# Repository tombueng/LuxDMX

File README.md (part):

<p align="center">
  
</p>

<h1 align="center">LuxDMX</h1>

<p align="center">
  <b>Open-source Art-Net / sACN (E1.31) &rarr; DMX512 gateway for ESP32 / ESP32-S3 / Ethernet.</b>
</p>

<p align="center">
  Its own web page shows all 512 channels live, FPS and jitter per sender, and warns you when
  <b>two consoles fight over a universe</b>. It does RDM too, and a basic one is about 10 EUR in parts.
</p>

<p align="center">

</p>

<p align="center">
  <a href="https://tombueng.github.io/LuxDMX/"><b>Flash from your browser</b></a> &nbsp;·&nbsp;
  <a href="https://luxdmx.org/video"><b>Watch the video</b></a> &nbsp;·&nbsp;
  <a href="#new-the-luxdmx-sequencer"><b>Sequencer</b></a> &nbsp;·&nbsp;
  <a href="hardware-carrier/README.md"><b>DIY carrier board</b></a> &nbsp;·&nbsp;
  <a href="#flashing-pre-built-firmware"><b>Install</b></a>
</p>

## News

**2026-11-12**

- Pixel lights cell by cell: single LEDs in cues, presets, groups and effects
- A console mode with a command line, fixture numbers, faders, encoders and MIDI learn
- Real gobos, prisms and beam angles in the 3D stage
- Endless pan/tilt, a roll axis, moving bars, and winches (they only move while armed)
- Render the 3D stage to a video, up to 8K
- Firmware: the OTA and AP passwords stay out of `/info.json`

Before that: the sequencer came out (11-04), LED rings and matrices (11-07), Apache-2.0 (11-10).
Everything else is in the [version history](CHANGELOG.md).

## New: the LuxDMX Sequencer

<p align="center">
  
</p>

A lighting console in a browser tab. Patch your lights (2,400 fixture types to search), build
looks, add some of the 72 effects and play the show from big buttons, your phone or a song's
timeline. There's a 3D stage, so you can program without any lights. No install, no account, and
your shows stay in your browser. If you know desks: there's a console mode with a command line
("1 thru 4 @ 50", "goto cue 5"), fixed fixture numbers, faders, encoders and MIDI learn, and pixel
lights can be programmed cell by cell (single LEDs of a bar, a ring or a matrix).

It plays a LuxDMX box straight from the page (the box serves a little bridge popup, firmware
v1.0.293 or newer) and any other Art-Net / sACN node through
[LuxDMX Link](sequencer/link/README.md), a small helper for Windows, macOS and Linux.

| | |
|---|---|
|  |  |
|  |  |

<p align="center"><b><a href="https://tombueng.github.io/LuxDMX/sequencer/">Open the Sequencer</a></b> &nbsp;·&nbsp; <a href="sequencer/README.md">What's in it</a> &nbsp;·&nbsp; <a href="sequencer/GUIDE.md">The guide</a></p>

---

| Status page | Settings page |
|---|---|
|  |  |

### The web UI

Manual channel control, labels, sparkline history, identify, blackout and the settings:

**[Watch the video](https://luxdmx.org/video)** &nbsp;·&nbsp; regenerate with [`docs/screenshot.mjs`](docs/screenshot.mjs)

---

## Features

### DMX output

| Feature | Details |
|---|---|
| **Art-Net → DMX512** | Full 512-channel, unicast or broadcast, universe configurable (0–15) |
| **sACN / E1.31 → DMX512** | Multicast receive, universe configurable, runs alongside Art-Net |
| **Protocol selection** | Art-Net only / sACN only / both, set in the web UI |
| **Up to 3 DMX outputs** | Three independent universes, each its own RS485 transceiver (the same universe on several = splitter). All three are RDM-capable |
| **Source merging** | Per-output HTP (highest takes precedence) / LTP (latest wins) / off, honouring the sACN priority field |
| **Signal-loss policy** | Per-output choice when the source stops: hold last frame (default), blackout, or stop sending. Continuous 40 Hz refresh bridges brief input gaps either way |
| **Configurable DMX pins** | Per output: universe, UART port, TX / RX / RTS GPIO, set in the web UI, no recompile |
| **Pixel output (WS281x)** | Drive addressable LED strip from Art-Net or sACN alongside DMX: up to 5 ports, multi-universe per port, WS2812/2815/2811 and SK6812 RGBW, colour order, brightness, gamma, per-port power cap with a live and all-white estimate, and ArtSync / E1.31 sync. Nothing is allocated for a port that is off. See [docs/pixels.md](docs/pixels.md) |

### RDM

| Feature | Details |
|---|---|
| **RDM (E1.20)** | Discover and configure fixtures on the wire: DISC_UNIQUE_BRANCH discovery, GET/SET DEVICE_INFO / DMX start address / identify / sensors, on an RDM-capable output (one with a DE/RE pin). esp_dmx-free RMT-TX + UART-RX engine |
| **RDM over Art-Net** | Full Art-Net 4 RDM output gateway (ArtPoll / ArtTodRequest / ArtTodControl / ArtRdm) so a console (DMX-Workshop, MagicQ, grandMA3, OLA) does RDM to the fixtures over the network. Discovery is scheduled one transaction per DMX frame, so RDM never stalls the DMX output. See [docs/rdm.md](docs/rdm.md) |

### Live diagnostics in the browser

| Feature | Details |
|---|---|
| **Live Web UI** | Bootstrap 5 dark theme, WebSocket push (~10/s), all 512 channels visible |
| **Sender list** | Shows all active Art-Net / sACN senders with per-sender FPS |
| **Conflict detection** | Warning banner when multiple senders are active simultaneously |
| **Jitter stat** | Real-time inter-frame timing deviation (EMA) |
| **Change log** | Live log of DMX value changes with top-N changed channels per frame |
| **Sparkline** | Per-channel history sparkline in the channel detail modal |
| **Channel labels** | Name any channel (e.g. "Front Wash L"), shown in the grid, the channel popup and the change log |

### Manual control

| Feature | Details |
|---|---|
| **Manual DMX control** | Click any channel in browser, set value via slider |
| **Art-Net / Manual toggle** | Switch between protocol passthrough and manual override |
| **Identify** | Flash a channel to full for ~1.5 s to physically locate the fixture |
| **Blackout button** | Zero all channels from the browser |

### Network

| Feature | Details |
|---|---|
| **Ethernet support** | WT32-ETH01 (LAN8720), the carrier board and the v6 board (W5500) run wired LAN *or* WiFi, switchable at runtime; any ESP32 / ESP32-S3 + an external SPI module (W5500 or DM9051) works too, and a **classic ESP32 can pick a SPI chip (W5500 / DM9051) or the built-in MAC + an RMII PHY** (LAN8720, IP101, RTL8201, DP83848, KSZ8081, JL1101) in `/config`; DHCP or static |
| **Selectable network mode** | Pick the interface (WiFi or wired Ethernet) and WiFi mode (client/STA or standalone AP) in the web UI, on boards that have both |
| **Static IP or DHCP** | Configurable static IP/gateway/subnet/DNS, or automatic DHCP |
| **Mesh-aware WiFi** | Scans all channels and joins the **strongest** AP (multi-AP/mesh friendly) |
| **First-run setup portal** | On first boot (or BOOT-button held) LuxDMX opens its own `LuxDMX-setup` access point with a captive portal. From there you either join your WiFi or run the device as its own access point, no router needed |
| **Standalone AP mode** | LuxDMX hosts its own WiFi network so a phone/tablet/console connects directly and sends Art-Net with no router (reachable at `192.168.4.1`) |
| **Wired link-loss policy** | Pick what happens if wired Ethernet is selected but the link is down: keep retrying (default, never opens a hotspot), a standalone WPA2 AP, reboot, or fall back to your saved WiFi network. A runtime watchdog applies it even if the cable is pulled mid-run, and the fallback AP never opens *unsecured*. The WiFi setup portal is BOOT-button-only (physical access), never an automatic fallback |
| **mDNS + DHCP hostname** | Reachable as `dmx-gateway.local` via mDNS, *and* the device sends its hostname over DHCP (option 12) so your router registers it by plain name. Clients without mDNS (e.g. Windows) can then reach it as `dmx-gateway` / `dmx-gateway.fritz.box`. Hostname configurable |

### Remote config from the console

| Feature | Details |
|---|---|
| **Remote node config (ArtAddress)** | Configure the node from the console's own network window (MagicQ Network Manager, DMX-Workshop, ...): rename it and move each output to a different universe, saved to NVS so it survives a reboot. On by default and **unauthenticated**, like every other Art-Net command. See [Remote node config over Art-Net](#remote-node-config-over-art-net-artaddress) |
| **Remote IP config (ArtIpProg)** | A controller can read and set the node's IP / mask / gateway (or switch it to DHCP) over the network with Art-Net `ArtIpProg`, so a box that landed on an unreachable address is recoverable without the BOOT button or a serial cable. **Off by default** (Art-Net has no auth, so on = anyone on the wire can renumber it); the new address applies on the next boot. See [Remote IP config over Art-Net](#remote-ip-config-over-art-net-artipprog-off-by-default) |

### On the box

| Feature | Details |
|---|---|
| **Status LED** | Plain GPIO, WS2812 RGB NeoPixel, or 5-LED panel (v6 board), all showing the same states: green = up (stays on; slow blink = DMX coming in), blue = RDM/identify **added on top of green** (both LEDs on the panel, cyan on a single RGB LED), orange = Ethernet-on-WiFi-fallback, red = no network, Knight-Rider boot |
| **Status display** | Optional I²C OLED (SSD1306 / SH1106) or colour SPI OLED (SSD1351): IP, universe, FPS, sources + auto-rotating conflict/identify/manual banners |
| **On-unit controls** | Optional rotary encoder and/or up to 4 buttons drive a small on-display menu to set the universe (and protocol) without a phone or PC, and the choice persists. Works with any mix of inputs: encoder only, one button, or the lot. See [docs/controls.md](docs/controls.md) |

### Updates, settings and API

| Feature | Details |
|---|---|
| **Versioned OTA** | Pick & install any past release from a table, or auto-update to latest |
| **OTA Updates** | ArduinoOTA (IDE/CLI) + manual `.bin` upload + one-click update from luxdmx.org |
| **NVS persistence** | Universe, protocol, IP config, labels, hostname, OTA password, LED/DMX pin config survive reboots |
| **Config backup / restore** | **`/config` → Backup & Restore**: download every setting plus the channel labels as one `.json`, restore it later or onto another box of the same kind. Passwords stay out unless you tick the box. A file may hold just a few settings; only those change. See [Backup and restore](#backup-and-restore) |
| **Config reset** | Hold BOOT button 3 s on startup, or via `/reset` page |
| **Remote restart** | Restart the box from the web UI (**Device → Restart device**) or `POST /reboot`, without changing a setting. Useful when a long-running gateway needs a nudge, or to free up memory before a firmware update |
| **REST API** | `GET /dmx.json`, `/senders.json`, `/log.json`, `/version.json`, `/labels.json` |
| **Browser bridge** | A web page can send DMX to the box (the [LuxDMX Sequencer](sequencer/README.md) does): the box serves `/bridge`, a tiny page the app opens as a popup, which asks you once per site and forwards frames over `/ws`. Shown as a sender with protocol **Web**, merged like any other source. See [Sending DMX from a web page](#sending-dmx-from-a-web-page-the-bridge) |
| **Phone as a remote** | The box serves `/remote`: a phone scans the sequencer's QR code and plays the laptop's live page (buttons, faders, GO, blackout) through the box. Held buttons let go by themselves if the phone drops out. See [A phone as a remote](#a-phone-as-a-remote) |

### Boards

| Feature | Details |
|---|---|
| **Firmware builds** | ESP32 (WROOM-32), ESP32-S3 (DevKitC-1), ESP32-S3 with octal PSRAM, WT32-ETH01. Plus a catalog of 30-odd boards in the `/config` pin picker, see [Visual pin configuration](#visual-pin-configuration-board-picker) |
| **DIY carrier board** | A 2-layer PCB for off-the-shelf modules: ESP32-S3 N16R8, up to 3 DMX/RDM ports, up to 5 pixel ports, W5500, OLED, encoder and buttons. Hand-solderable, a few bucks in parts. See [Hardware](#hardware) |

---

## Hardware

The easy way to a real LuxDMX box is the carrier board below: order the PCB, plug in modules,
solder a few small parts. If you just want to try it tonight, skip to the
[breadboard build](#breadboard-build-no-pcb), that's an ESP32 and one RS-485 module on jumper wires.

> ### The LuxDMX carrier board
>
> The DIY path, for a few bucks. A 2-layer PCB that off-the-shelf modules plug into: an
> **ESP32-S3-DevKitC-1 N16R8**, up to three **MAX3485** RS-485 modules, a **USR-ES1 W5500** for
> wired Ethernet and a **1.3" SH1106 OLED**. The rotary encoder and two buttons sit right on the
> board. Everything else is a handful of small parts on the back, and those are all optional
> except the ones for what you actually use.
>
> - **DMX + RDM on up to 3 ports**, one RS-485 module per port, direction pin driven so RDM works
> - **WS281x pixels on up to 5 ports** once you add the 74HCT541 buffer chip. It lifts the S3's
>   3.3 V data to the 5 V the strips want, so no pixels without it
> - **WiFi**, or wired Ethernet when the W5500 module is fitted
> - 12/24 V pixel supply with a fuse on the board; the logic runs off USB, an external 5 V or a
>   little buck module off the pixel supply
> - 100 x 80 mm, any fab. Hand soldering only, and the lands take anything from 0402 to 1206, so
>   use whatever's in your drawer
>
> A one-port WiFi DMX node is around 10 EUR of parts off AliExpress, plus the PCB. Ethernet and the
> display add another 6 to 11.
>
> Most of the firmware testing happens on this board. The DMX ports are **not galvanically
> isolated** (plain MAX3485 modules, TVS diodes on the lines). Fine for a desk or a small rig. If
> you need isolation, the breadboard build with the Waveshare module has it.
>
> 
>
> **→ Gerbers, BOM with LCSC numbers, assembly guide and the current math: [`hardware-carrier/`](hardware-carrier/README.md)**

### Carrier: what plugs in

| Module | Search for | Watch out |
|---|---|---|
| ESP32-S3 dev board | `ESP32-S3-DevKitC-1 N16R8` | Get the N16R8 (16 MB flash, 8 MB octal PSRAM), that's what the carrier build expects. The socket rows are **25.4 mm** apart, one pitch wider than Espressif's own DevKitC-1 (22.86 mm), which is what the common dual USB-C clones have. Hold the seller's photo against a 1:1 print of the footprint before you buy |
| RS-485, one per DMX port | `MAX3485 TTL to RS485 module 3.3V` | The bench board runs the RAKSTORE one, silk `RS485 V2.01`. Needs the **EN pin**, without it there is no RDM. Most carry 120 Ω and bias already, see the terminator below |
| Ethernet (optional) | `USR-ES1 W5500` | Two rows of 6 pins. The W5500 boards with 8 pins in one row are a different module |
| Display (optional) | `1.3 inch OLED I2C SH1106` | Sits on a 1x4 female socket. These ship with VCC and GND in either order, check its own silk |

### Carrier: optional parts

Only the ESP32 module is mandatory. A two-port DMX node without pixels leaves more than half the
board empty. The small parts all sit on the back under the modules, so solder those first, then the
headers.

| Part | Fit it when |
|---|---|
| **DMX, per port** | |
| MAX3485 module + 3-pin header (or a 2.54 mm screw terminal) | you use that port |
| 10k on DE/RE | you use that port. Keeps the driver off the bus while the ESP boots |
| 120 Ω terminator | that port is at the **end** of the bus, and the module doesn't already have one (a second one puts 60 Ω on the bus) |
| 2 × 330 Ω fail-safe bias | the port drives its bus, which it normally does. Once per bus, so leave it out if the module already biases the line |
| 2 × TVS diode (SMF12CA or SMAJ12CA) | the port leaves the enclosure |
| **Pixels** | |
| 74HCT541 buffer (SO-20 wide) | at least one pixel port is used. **HCT**, not HC: the HC parts don't switch reliably on 3.3 V. And not the `PW` (TSSOP) version LCSC stocks most of, it won't land |
| 330 Ω series resistor, per port | you use that pixel port. Damps the ringing on the strip wire |
| 3-pole screw terminal, per port | you use that pixel port |
| 1000 µF 35 V, `12-24V IN` terminal, fuse | any pixel port is used, see power below |
| **Network and UI** | |
| W5500 module + 2 × 10k pull-ups + 100 nF / 1 µF / 22 µF | you want wired Ethernet |
| 1.3" OLED | you want the display |
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
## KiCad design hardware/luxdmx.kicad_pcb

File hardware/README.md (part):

> [!NOTE]
> **v6 has not been fabricated yet.** The board is on `master`, design-complete, and passes the full
> scripted validation (DRC, isolation, SPICE, Ethernet skew, header parity; see **VALIDATION.md**).
> An earlier spin of this design was built and came up working (rails, galvanic isolation, PoE
> standalone, both DMX universes bit-exact, RDM 64/64 on both lines), but v6 carries changes that
> have not been on physical copper yet: native USB instead of a CH340 bridge, TPS2116 priority mode,
> a 3225 crystal package, and the J4/J6 header re-pin. Those are what the first v6 article has to
> prove. Treat it as a prototype: the firmware on a plain ESP32 + an isolated RS-485 module is still
> the longest-proven path (see the main README). The ruggedization pass (USB ESD, PTC fuse, +5V TVS,
> a TPS2116 priority power mux, DMX common-mode chokes, ferrite supply filters), plated GND mounting
> holes, wider power traces, and the DMX512-A "Protected" series-TBU front end are all in.

# LuxDMX v6 — hardware

A compact, open-source **Art-Net / sACN → galvanically-isolated DMX512 gateway**, built around
an ESP32-S3 with **both** WiFi *and* wired Ethernet. Designed entirely as code (SKiDL netlist) and
routed by a fully-scripted, placement-driven pipeline — so the board regenerates itself from your
component placement, isolation barrier and all.

---

## What problem does it solve?

Lighting consoles and media servers speak **Art-Net** or **sACN (E1.31)** over a network. Fixtures —
dimmers, moving heads, hazers, LED bars — speak **DMX512** over an isolated RS-485 bus. LuxDMX sits
between them: it receives Art-Net/sACN over WiFi or Ethernet and emits a clean, **opto-isolated DMX512**
signal. It's the box that lets you drive a rack of conventional stage gear from QLab, a grandMA, or any
Art-Net source — without dragging a laptop and a USB-DMX dongle around backstage.

The whole device runs on a single ESP32-S3, fits on a board you can hold in your palm, and costs a few
dollars to fabricate at JLCPCB.

---

## Headline design decisions (the "why")

| Decision | Why |
|---|---|
| **ESP32-S3** as the MCU | Plenty of GPIO, fast dual-core, native USB, mature Arduino/IDF support, and cheap. The **N8R2** brings 8 MB flash + **2 MB PSRAM**, and because that PSRAM is **quad**, it leaves **GPIO35–37** free for the expansion header. Only the **octal**-PSRAM parts (R8 and up) wire GPIO33–37 to the memory and lose them. |
| **W5500 SPI Ethernet** (not the ESP's RMII) | The S3 has **no built-in Ethernet MAC** (unlike the original ESP32), so RMII/LAN8720 is physically impossible. The W5500 is a self-contained TCP/IP-offload Ethernet controller on SPI — the *only* practical wired-Ethernet path for the S3. Wired Ethernet matters: a packed venue's 2.4 GHz band is hostile, and a show can't drop frames. |
| **Galvanically-isolated DMX** | DMX runs long cables between gear sitting on different mains circuits with different ground potentials. Without isolation you get **ground loops** (noise, flicker) and, worse, **fault currents** that can destroy the gateway when something downstream shorts. Pro DMX gear is *always* isolated. We isolate both the data (ISO3086) and the power feeding it (B0505S DC-DC), so the DMX domain shares **no copper** with the logic side. |
| **USB-C** | Reversible, modern, and carries both **power and native flashing** — one cable to power and program. |
| **4-layer PCB** | A solid inner ground plane gives the W5500's Ethernet pairs a 100 Ω reference, tames EMI, and makes the dense routing actually fit. (More below.) |

---

## The components, in detail

### Brains & networking
- **U1 — ESP32-S3-WROOM-1-N8R2** *(LCSC C2913204; 8 MB flash + 2 MB quad PSRAM)* — the MCU + 2.4 GHz WiFi radio. Runs the Art-Net/sACN
  receiver, the web UI, OTA updates, and the DMX engine. The PCB antenna hangs over the left board edge
  (no copper underneath it — intentional, for radiation efficiency).
- **U2 — WIZnet W5500** *(C32843)* + **Y1 — 25 MHz crystal, 3225** *(C9006, CL = 12 pF, load caps C12/C13 = 18 pF C0G)* + **J3 — HY931147C PoE RJ45 MagJack** *(C91754)* —
  a complete 10/100 wired-Ethernet subsystem on SPI. The magjack integrates the isolation magnetics,
  the link/activity LEDs, **and an internal PoE rectifier** (Mode A + Mode B → a single rectified DC pair
  on pins 9/10 — see *Power*). (Ethernet is isolated by the magjack's transformers; the W5500's
  current-mode TX center-tap is biased to 3V3 on the chip-side tap, independent of the PoE extraction
  on the cable side.)

### Isolated DMX output — two independent universes
Each universe is a self-contained galvanic island; the two share no copper with each other or the logic side.
- **U5 / U6 — TI ISO3086DWR** *(C183095)* — the **isolated RS-485 transceivers** (one per universe). The DMX
  driver and the logic that controls it are separated by a silicon isolation barrier rated for kilovolts.
  Wired 2-wire (Y↔A, Z↔B bridged) for standard DMX512. Universe 1 on UART/port 1, universe 2 on port 2.
- **PS1 / PS2 — B0505S-1W** *(C7465127)* — the **isolated 5 V→5 V DC-DC** modules powering the *secondary*
  side of U5 / U6. Because both the data path **and** its power are isolated, each DMX connector shares no
  ground with anything else.
- **D1 / D7 — SM712 TVS** *(C404012)* + **R12 / R19 — 120 Ω termination** — per-universe surge protection
  clamped to that universe's isolated ground, and the standard RS-485 line termination.
- **F2–F5 — Bourns TBU-CA065-200-WH** *(C913221)* — a series **high-speed protector** on each DMX data line:
  the DMX512-A **"Protected"** (E1.11 Annex C) front end. It blocks a sustained fault (someone plugging mains,
  or up to ±42 V, into the XLR) in under a microsecond and self-recovers, so the SM712 only ever sees the
  sub-microsecond transient. Full breakdown in [`E1.11_COMPLIANCE.md`](E1.11_COMPLIANCE.md).
- **R20–R23 — 470 Ω fail-safe bias** — hold each idle DMX pair in the RS-485 fail-safe state (needed for RDM).
- **J1 / J5 — XLR-5** *(C368501)* — the two DMX output connectors (Neutrik NC5FAH), each living entirely on its isolated domain.
- Nets: universe 1 = `VISO`/`GNDISO`/`DMX_A`/`DMX_B`; universe 2 = `VISO2`/`GNDISO2`/`DMX2_A`/`DMX2_B`.

### Power — USB-C **or** PoE (PoE has priority)
- **PoE (802.3af):** the **J3** magjack rectifies PoE internally and outputs DC on **`VPOE+`/`VPOE-`** →
  **U7 — SDAPO DP9900M-5V** *(C5380106)*, an **isolated PD + DC-DC module** (36–57 V in, regulated 5 V out,
  1.5 kV isolation, class 0 ≈ 13 W — far more than this board's ~2–3 W). **D10 — SMAJ58A** *(C110521)* clamps
  surges on the rectified rail. The module's `-VDC` becomes board GND; its `+VDC` is the PoE 5 V source.
- **5 V source select:** **U9 — TPS2116** power mux feeds the board **`+5V`** rail from either the **PoE 5 V**
  (`+5V_POE`, on VIN1) or the **USB-C 5 V** (`+5V_USB`, through the F1 PTC, on VIN2), with no backfeed. It runs
  in **priority mode**: `MODE` is tied to VIN1, so **PoE wins whenever it is present** and the board falls back
  to USB only when PoE goes away. The **PR1 divider (R24 = 30 kΩ / R25 = 10 kΩ)** sets the VIN1 switchover
  threshold to **Vsw = 4.0 V** (VREF 1.0 V × (30 + 10) / 10). Vsw is deliberately high, because VOUT tracks VIN1
  down until the switch actually fires: at 4.0 V the `+5V` rail stays far above the ESP's ~2.8 V hang threshold
  while PoE collapses. The pass-FET drop is only ~30 mV (vs ~0.4 V for a Schottky), so `+5V` stays ≈ 4.9 V on
  USB and the B0505S / ISO3086 VCC2 rail clears its 4.5 V minimum across the whole USB range. Input caps
  **C30 / C31** (1 µF), bulk **C29** (22 µF).
  *(The first article tied `MODE`/`PR1` to GND, which is the default "higher voltage wins" mode. With two
  near-equal 5 V sources that hunts, and a PoE→USB handover hung the board. Priority mode is that fix.)*
- **U4 — SY8089 buck** *(C78988)* + **L1 — 2.2 µH** — steps the muxed 5 V down to **3.3 V**. The feedback
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
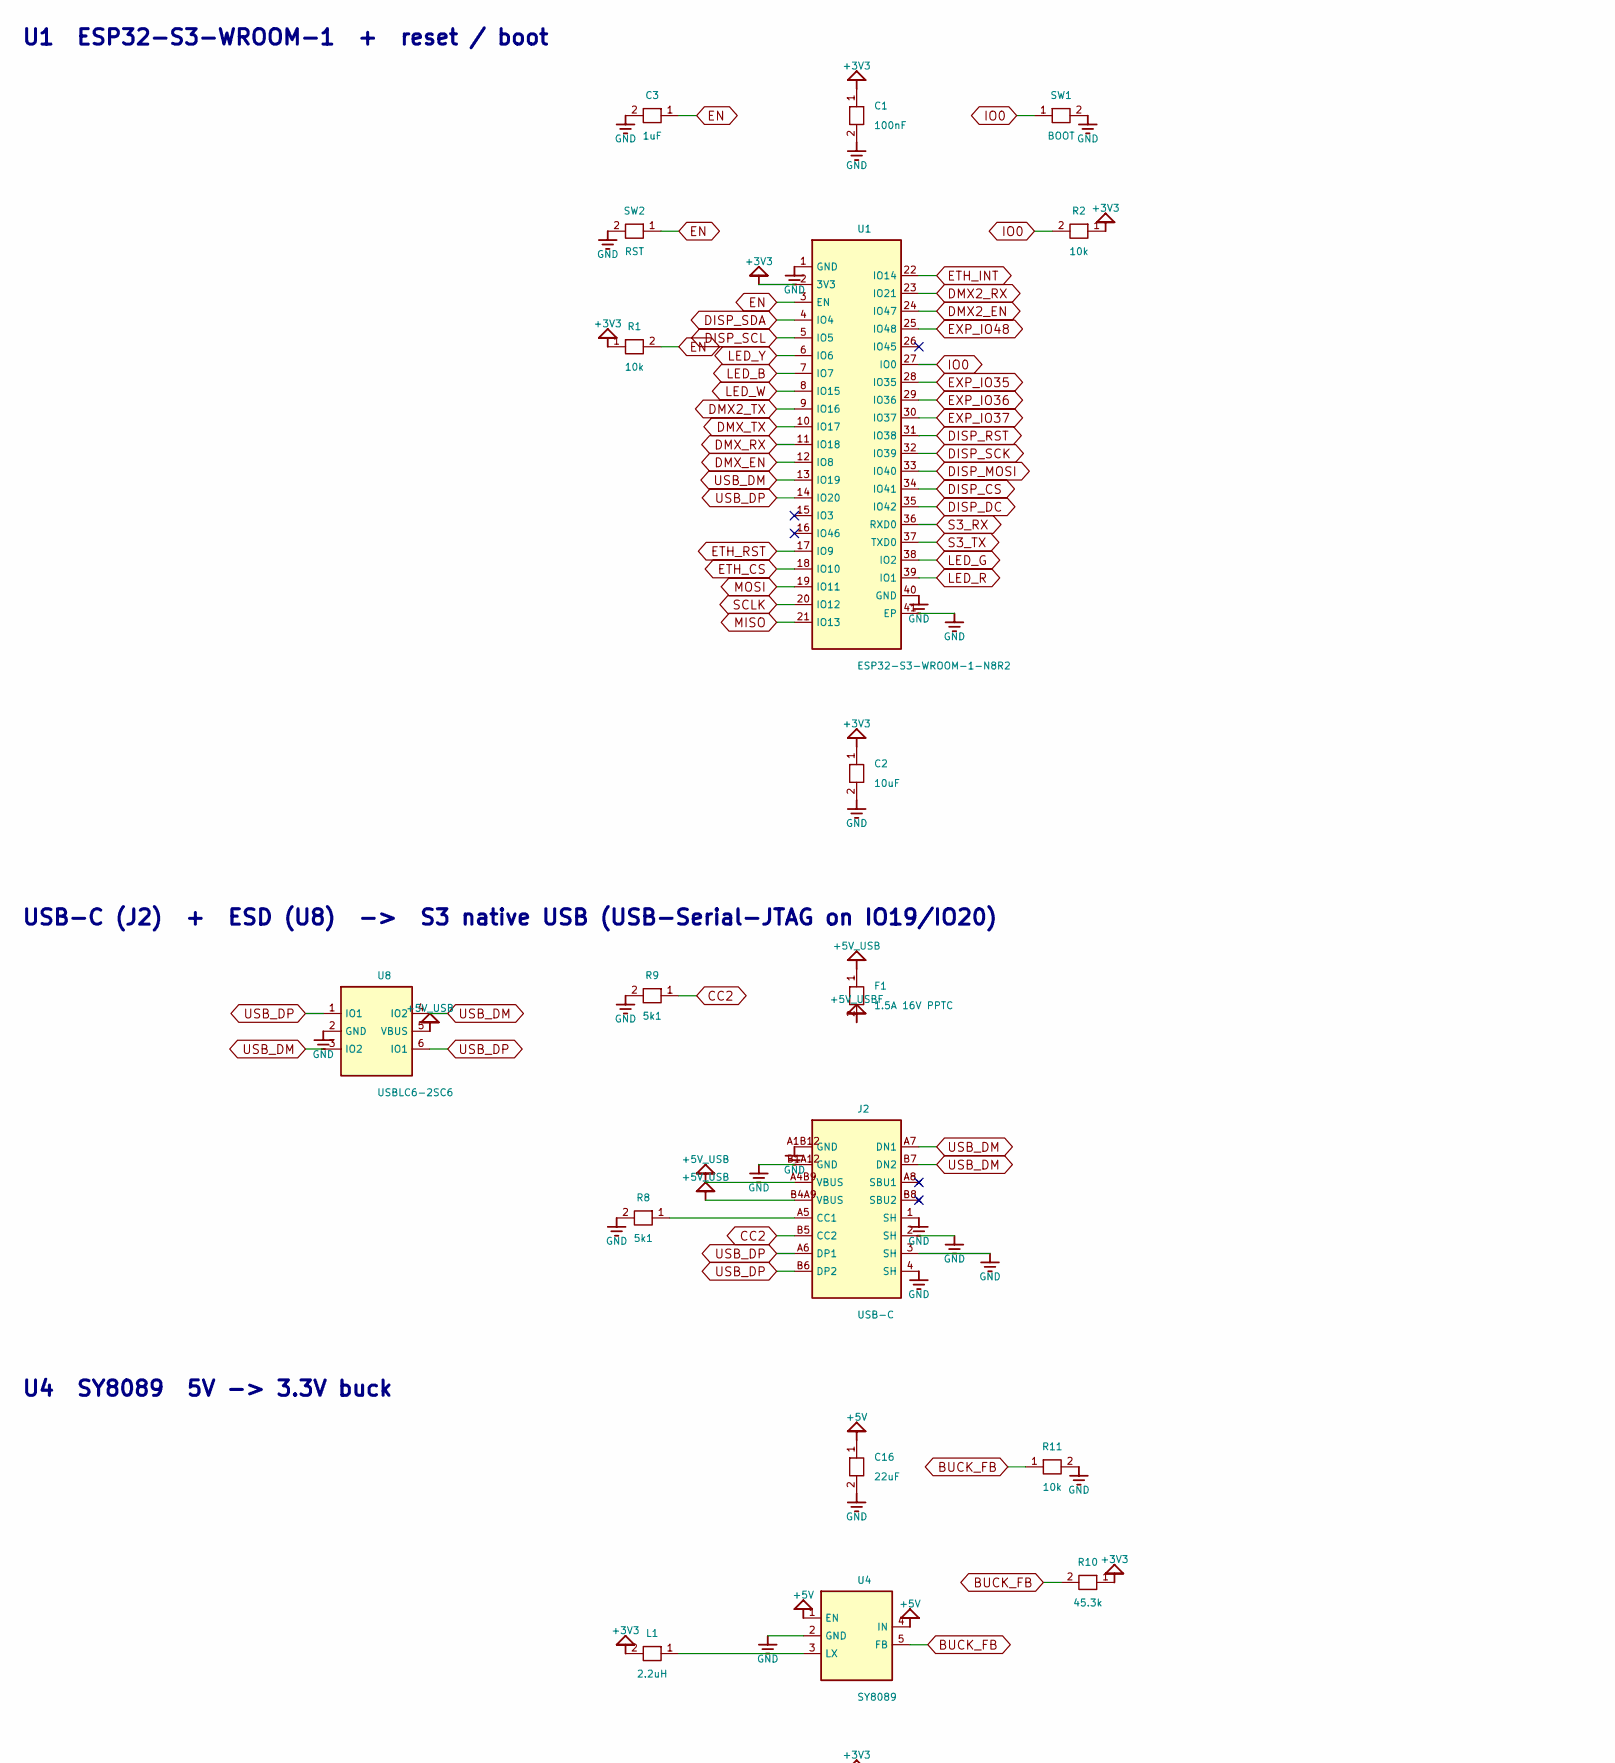
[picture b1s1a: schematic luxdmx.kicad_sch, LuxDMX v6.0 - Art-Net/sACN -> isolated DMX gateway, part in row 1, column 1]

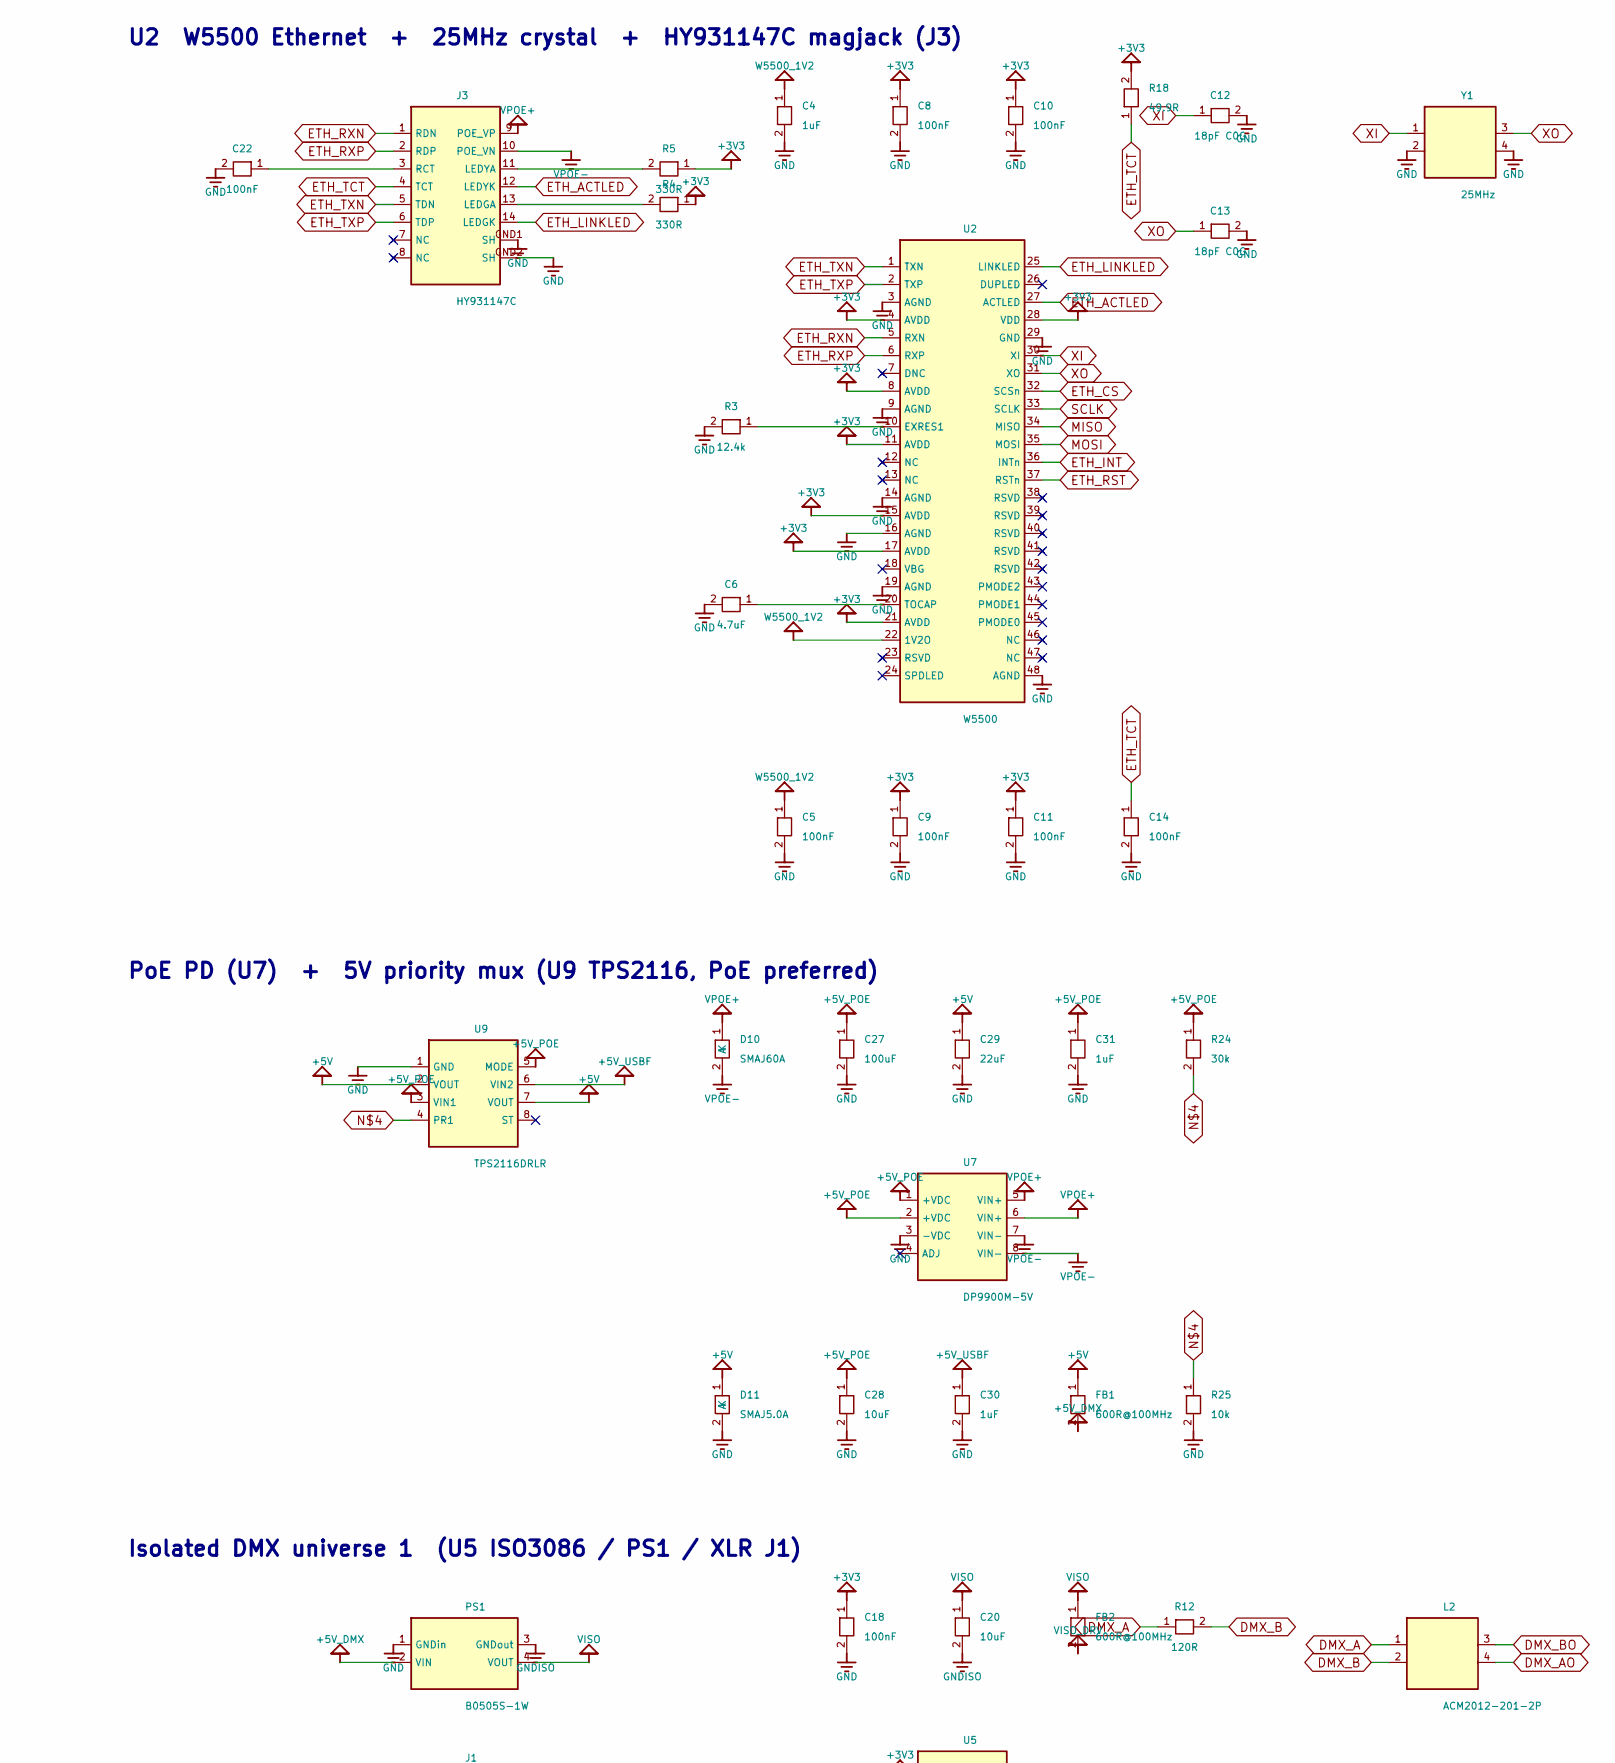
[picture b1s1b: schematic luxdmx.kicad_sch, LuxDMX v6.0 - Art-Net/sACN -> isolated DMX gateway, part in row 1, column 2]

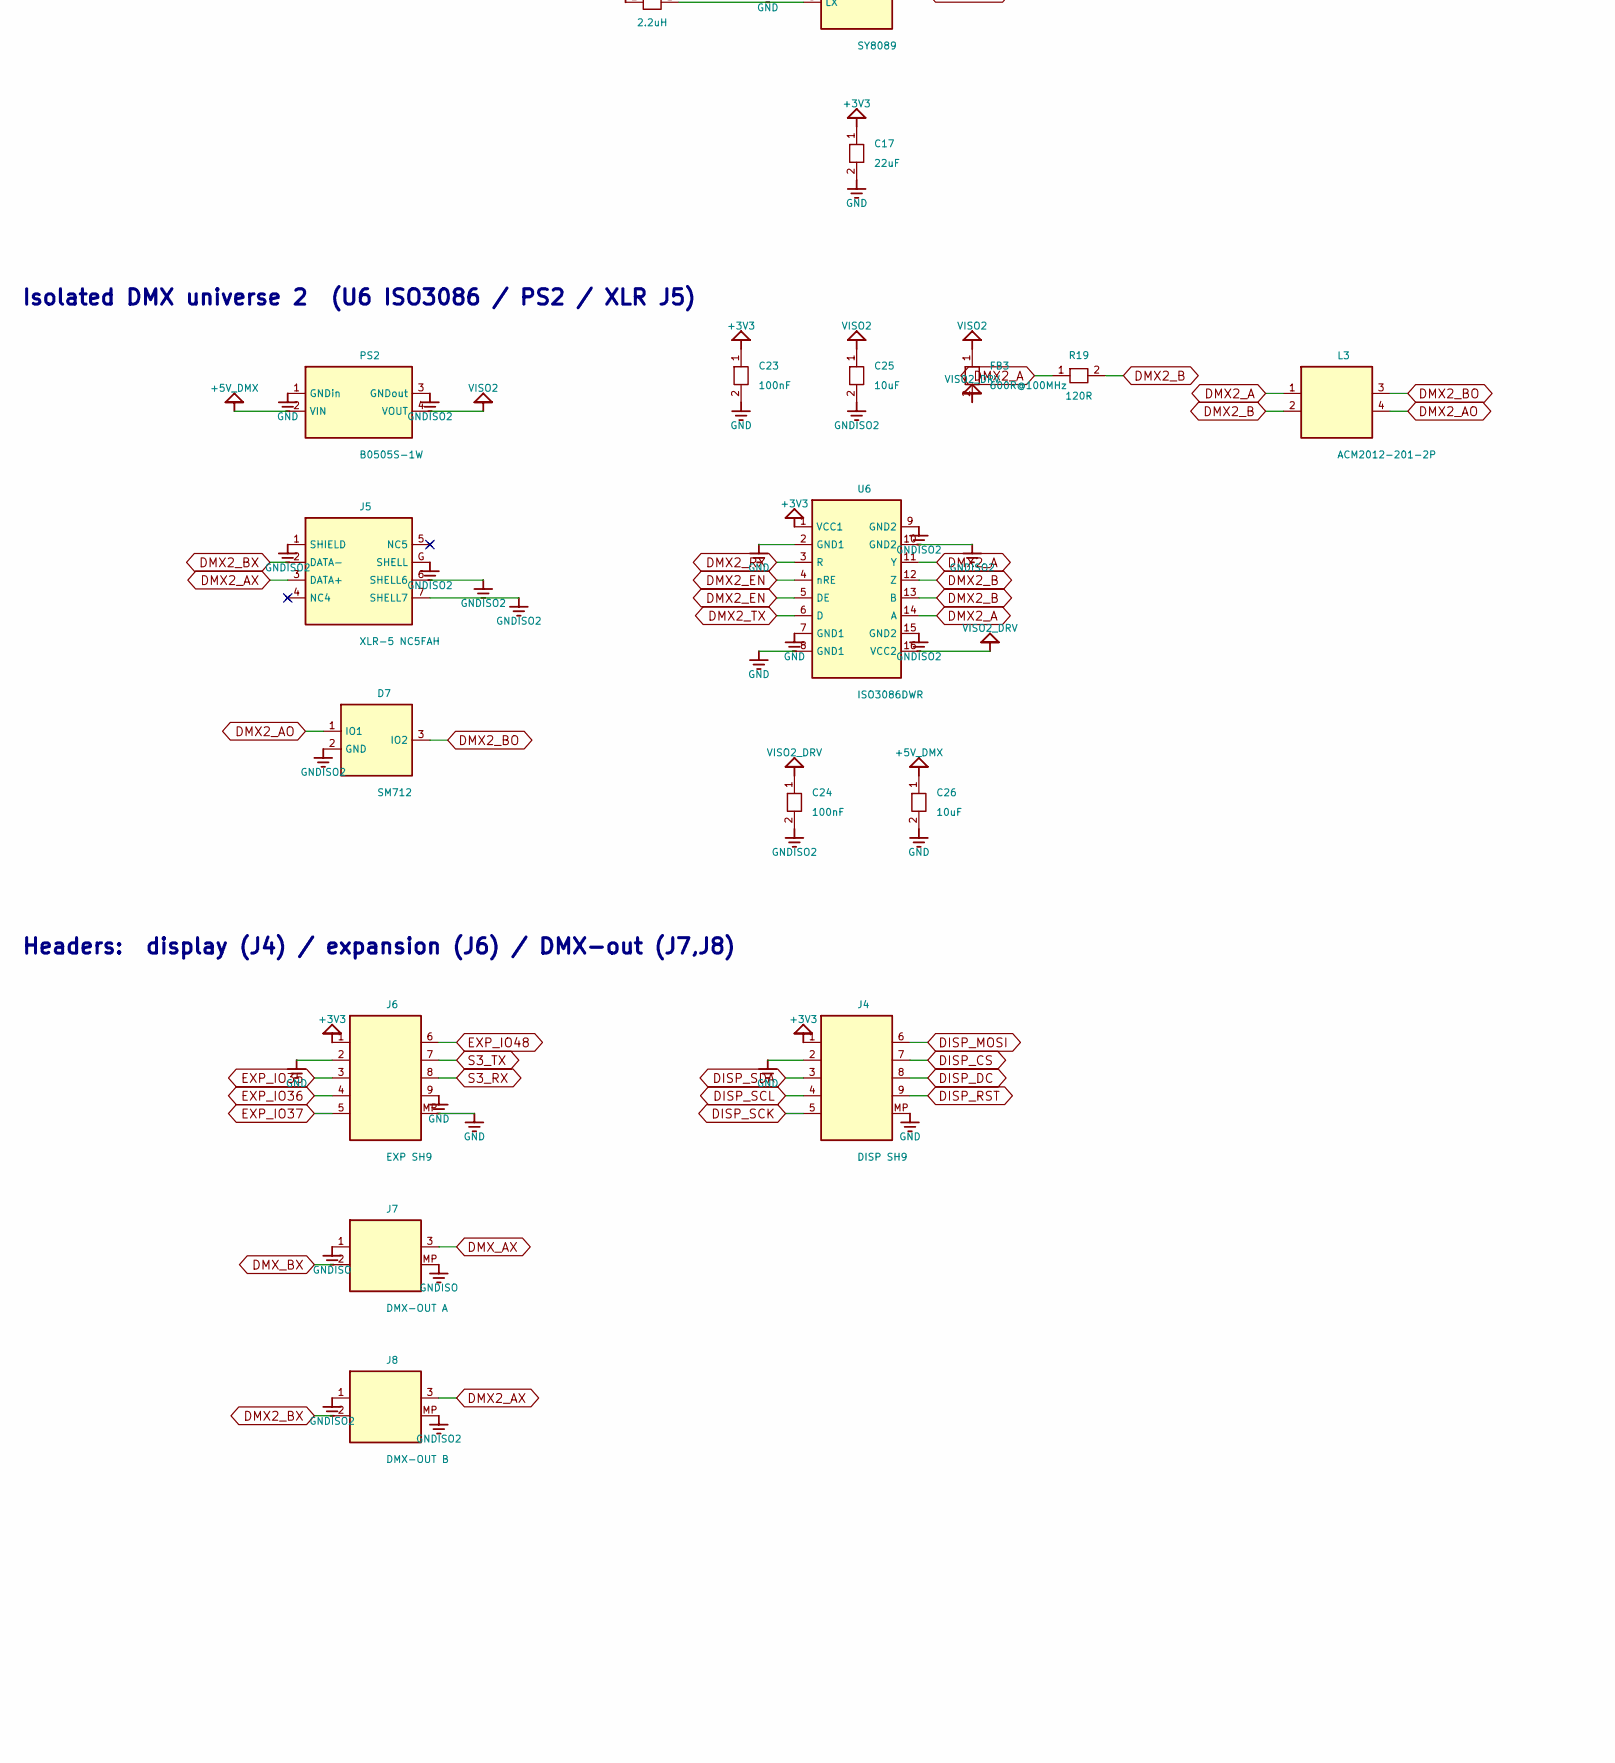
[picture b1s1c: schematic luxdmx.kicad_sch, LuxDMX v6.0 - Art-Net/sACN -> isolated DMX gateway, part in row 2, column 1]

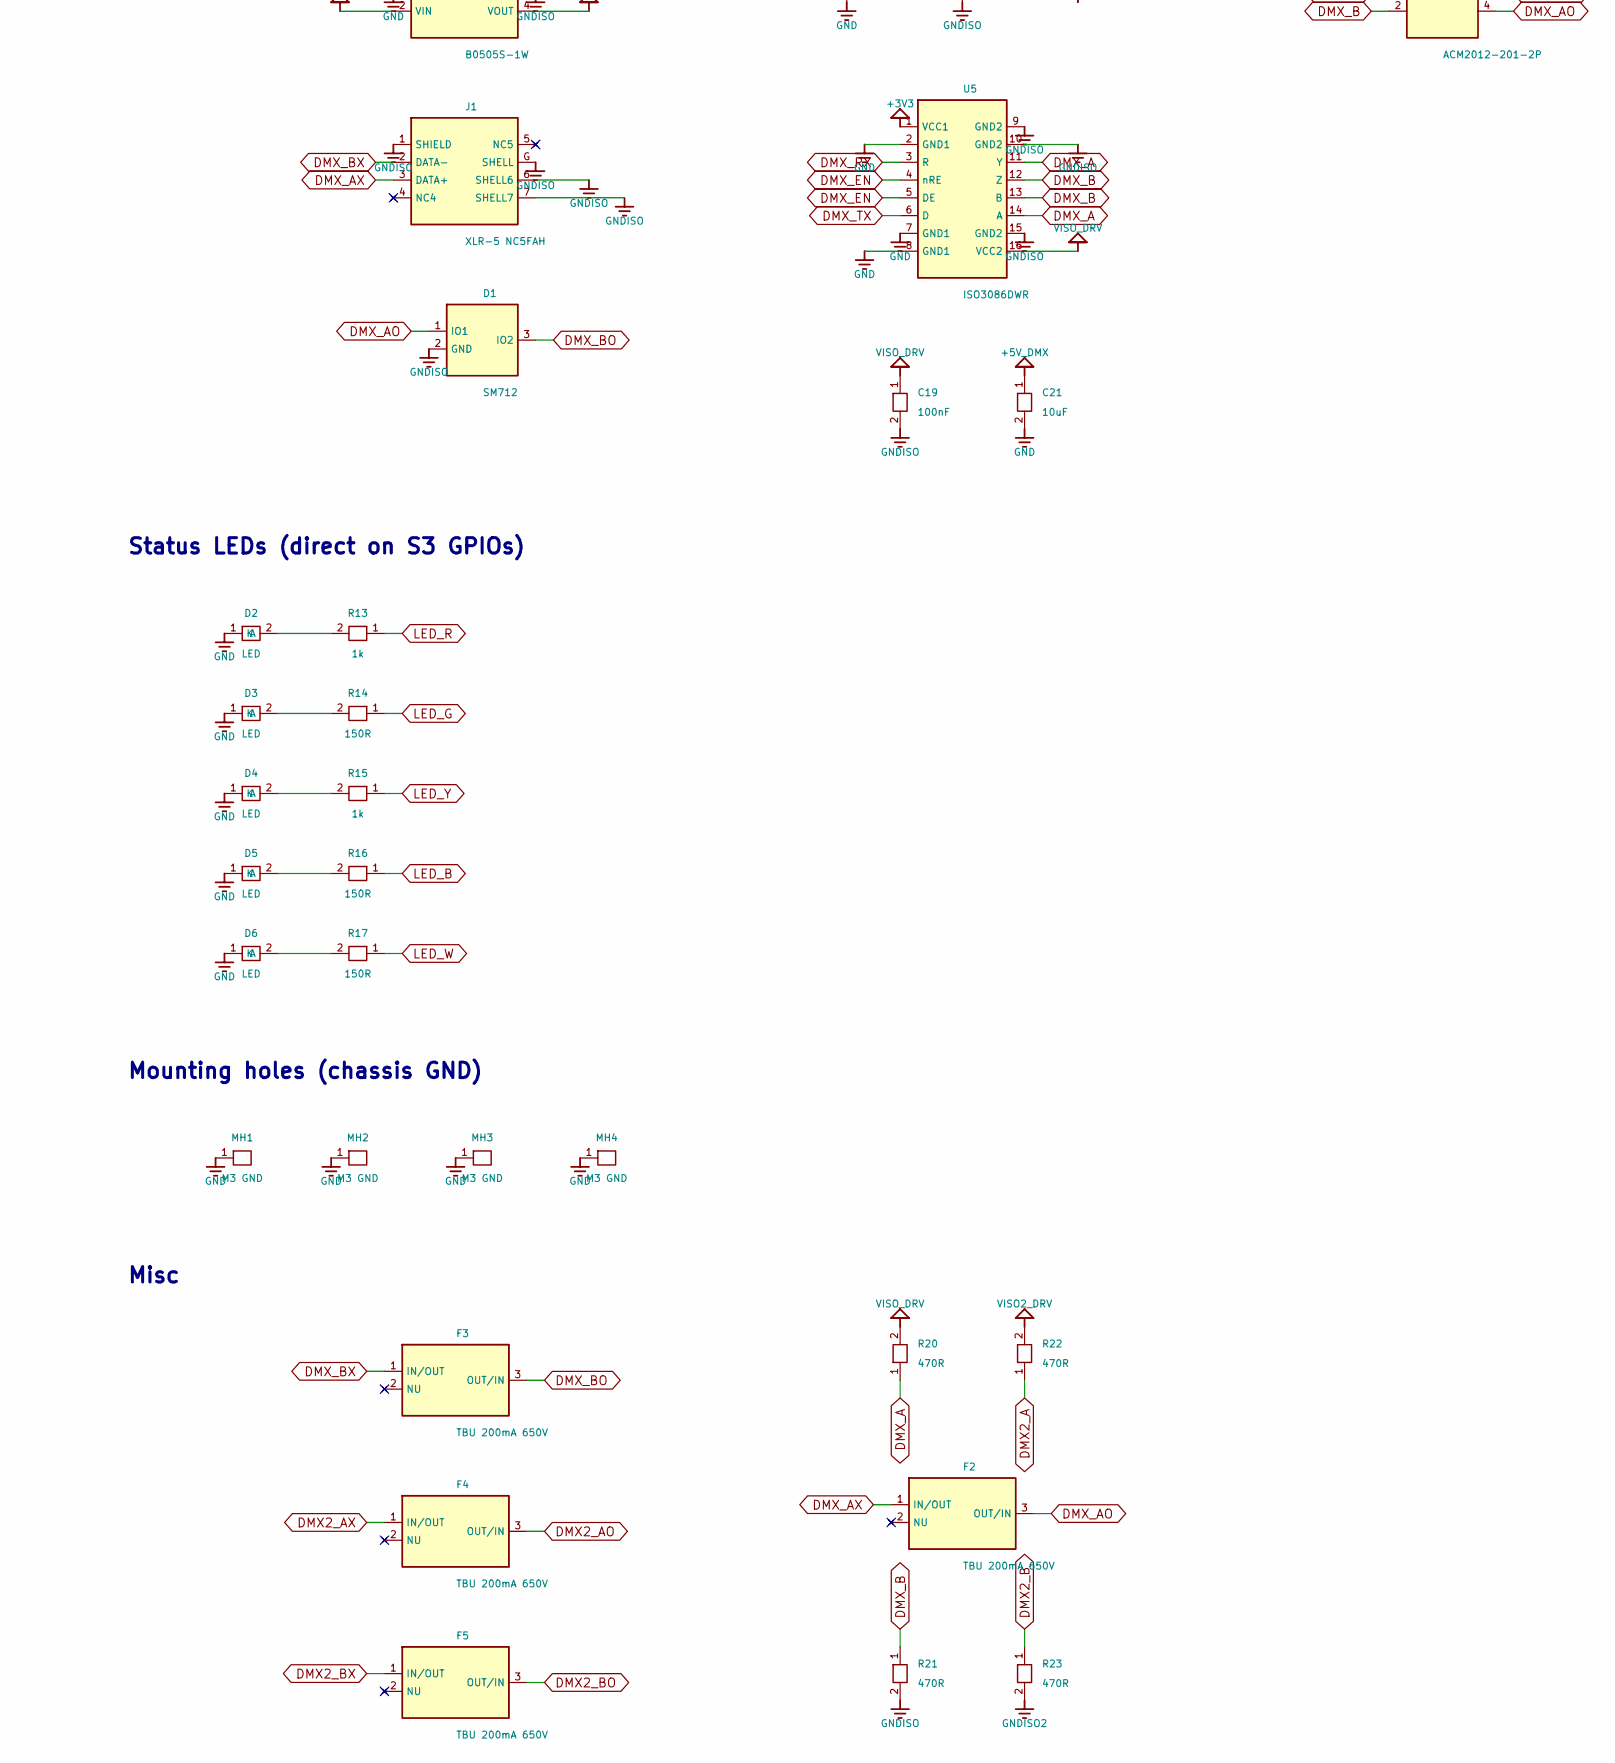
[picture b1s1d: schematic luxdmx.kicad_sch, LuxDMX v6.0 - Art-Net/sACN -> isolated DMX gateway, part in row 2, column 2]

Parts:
C1, C5, C8, C9, C10, C11, C14, C18, C19, C22, C23, C24: 100nF; C_0402_1005Metric
C2, C28: 10uF; C_0805_2012Metric
C3, C4: 1uF; C_0402_1005Metric
C6: 4.7uF; C_0402_1005Metric
C12, C13: 18pF C0G; C_0402_1005Metric
C16, C17, C29: 22uF; C_0805_2012Metric
C20, C21, C25, C26: 10uF; C_1206_3216Metric
C27: 100uF; CP_Elec_6.3x7.7
C30, C31: 1uF; C_0603_1608Metric
D1, D7: SM712; SOT-23
D2, D3, D4, D5, D6: LED; LED_0603_1608Metric
D10: SMAJ60A; D_SMA
D11: SMAJ5.0A; D_SMA
F1: 1.5A 16V PPTC; Fuse_1206_3216Metric
F2, F3, F4, F5: TBU 200mA 650V; DIO-SMD_3P-L6.5-W4.0-BI
FB1, FB2, FB3: 600R@100MHz; L_0805_2012Metric
J1, J5: XLR-5 NC5FAH; CONN-TH_NC5FAH
J2: USB-C; USB-C_SMD-TYPE-C-31-M-12_1
J3: HY931147C; RJ45-TH_HY931147C
J4: DISP SH9; JST_SH_SM09B-SRSS-TB_1x09-1MP_P1.00mm_Horizontal
J6: EXP SH9; JST_SH_SM09B-SRSS-TB_1x09-1MP_P1.00mm_Horizontal
J7: DMX-OUT A; JST_SH_SM03B-SRSS-TB_1x03-1MP_P1.00mm_Horizontal
J8: DMX-OUT B; JST_SH_SM03B-SRSS-TB_1x03-1MP_P1.00mm_Horizontal
L1: 2.2uH; IND-SMD_L4.0-W4.0
L2, L3: ACM2012-201-2P; L_CommonModeChoke_Coilank_ACM2012
MH1, MH2, MH3, MH4: M3 GND; MountingHole_3.2mm_M3_Pad
PS1, PS2: B0505S-1W; PWRM-TH_B0505S-1W
R1, R2, R11, R25: 10k; R_0402_1005Metric
R3: 12.4k; R_0402_1005Metric
R4, R5: 330R; R_0402_1005Metric
R8, R9: 5k1; R_0402_1005Metric
R10: 45.3k; R_0402_1005Metric
R12, R19: 120R; R_0805_2012Metric
R13, R15: 1k; R_0402_1005Metric
R14, R16, R17: 150R; R_0402_1005Metric
R18: 49.9R; R_0402_1005Metric
R20, R21, R22, R23: 470R; R_0402_1005Metric
R24: 30k; R_0402_1005Metric
SW1: BOOT; SW_SPST_B3U-1000P
SW2: RST; SW_SPST_B3U-1000P
U1: ESP32-S3-WROOM-1-N8R2; ESP32-S3-WROOM-1
U2: W5500; LQFP-48_L7.0-W7.0-P0.50-LS9.0-BL
U4: SY8089; SOT-23-5_L3.0-W1.7-P0.95-LS2.8-BR
U5, U6: ISO3086DWR; SOIC-16_L10.3-W7.5-P1.27-LS10.3-BL
U7: DP9900M-5V; PWRM-SMD_DP9900M-5V
U8: USBLC6-2SC6; SOT-23-6
U9: TPS2116DRLR; SOT-583-8
Y1: 25MHz; Crystal_SMD_3225-4Pin_3.2x2.5mm

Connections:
+3V3: C1.1, C2.1, C8.1, C9.1, C10.1, C11.1, C17.1, C18.1, C23.1, J4.1, J6.1, L1.2, R1.1, R2.1, R4.1, R5.1, R10.1, R18.2, U1.2 (3V3), U2.4 (AVDD), U2.8 (AVDD), U2.11 (AVDD), U2.15 (AVDD), U2.17 (AVDD), U2.21 (AVDD), U2.28 (VDD), U5.1 (VCC1), U6.1 (VCC1)
+5V: C16.1, C29.1, D11.1 (K), FB1.1, U4.1 (EN), U4.4 (IN), U9.2 (VOUT), U9.7 (VOUT)
+5V_DMX: C21.1, C26.1, FB1.2, PS1.2 (VIN), PS2.2 (VIN)
+5V_POE: C27.1, C28.1, C31.1, R24.1, U7.1 (+VDC), U7.2 (+VDC), U9.3 (VIN1), U9.5 (MODE)
+5V_USB: F1.1, J2.A4B9 (VBUS), J2.B4A9 (VBUS), U8.5 (VBUS)
+5V_USBF: C30.1, F1.2, U9.6 (VIN2)
BUCK_FB: R10.2, R11.1, U4.5 (FB)
BUCK_LX: L1.1, U4.3 (LX)
CC1: J2.A5 (CC1), R8.1
CC2: J2.B5 (CC2), R9.1
DISP_CS: J4.7, U1.34 (IO41)
DISP_DC: J4.8, U1.35 (IO42)
DISP_MOSI: J4.6, U1.33 (IO40)
DISP_RST: J4.9, U1.31 (IO38)
DISP_SCK: J4.5, U1.32 (IO39)
DISP_SCL: J4.4, U1.5 (IO5)
DISP_SDA: J4.3, U1.4 (IO4)
DMX2_A: L3.1, R19.1, R22.1, U6.11 (Y), U6.14 (A)
DMX2_AO: D7.1 (IO1), F4.3 (OUT/IN), L3.4
DMX2_AX: F4.1 (IN/OUT), J5.3 (DATA+), J8.3
DMX2_B: L3.2, R19.2, R23.1, U6.12 (Z), U6.13 (B)
DMX2_BO: D7.3 (IO2), F5.3 (OUT/IN), L3.3
DMX2_BX: F5.1 (IN/OUT), J5.2 (DATA-), J8.2
DMX2_EN: U1.24 (IO47), U6.4 (nRE), U6.5 (DE)
DMX2_RX: U1.23 (IO21), U6.3 (R)
DMX2_TX: U1.9 (IO16), U6.6 (D)
DMX_A: L2.1, R12.1, R20.1, U5.11 (Y), U5.14 (A)
DMX_AO: D1.1 (IO1), F2.3 (OUT/IN), L2.4
DMX_AX: F2.1 (IN/OUT), J1.3 (DATA+), J7.3
DMX_B: L2.2, R12.2, R21.1, U5.12 (Z), U5.13 (B)
DMX_BO: D1.3 (IO2), F3.3 (OUT/IN), L2.3
DMX_BX: F3.1 (IN/OUT), J1.2 (DATA-), J7.2
DMX_EN: U1.12 (IO8), U5.4 (nRE), U5.5 (DE)
DMX_RX: U1.11 (IO18), U5.3 (R)
DMX_TX: U1.10 (IO17), U5.6 (D)
EN: C3.1, R1.2, SW2.1, U1.3 (EN)
ETH_ACTLED: J3.12 (LEDYK), U2.27 (ACTLED)
ETH_CS: U1.18 (IO10), U2.32 (SCSn)
ETH_INT: U1.22 (IO14), U2.36 (INTn)
ETH_LINKLED: J3.14 (LEDGK), U2.25 (LINKLED)
ETH_RCT: C22.1, J3.3 (RCT)
ETH_RST: U1.17 (IO9), U2.37 (RSTn)
ETH_RXN: J3.1 (RDN), U2.5 (RXN)
ETH_RXP: J3.2 (RDP), U2.6 (RXP)
ETH_TCT: C14.1, J3.4 (TCT), R18.1
ETH_TXN: J3.5 (TDN), U2.1 (TXN)
ETH_TXP: J3.6 (TDP), U2.2 (TXP)
EXP_IO35: J6.3, U1.28 (IO35)
EXP_IO36: J6.4, U1.29 (IO36)
EXP_IO37: J6.5, U1.30 (IO37)
EXP_IO48: J6.6, U1.25 (IO48)
GND: C1.2, C2.2, C3.2, C4.2, C5.2, C6.2, C8.2, C9.2, C10.2, C11.2, C12.2, C13.2, C14.2, C16.2, C17.2, C18.2, C21.2, C22.2, C23.2, C26.2, C27.2, C28.2, C29.2, C30.2, C31.2, D2.1 (K), D3.1 (K), D4.1 (K), D5.1 (K), D6.1 (K), D11.2 (A), J2.1 (SH), J2.2 (SH), J2.3 (SH), J2.4 (SH), J2.A1B12 (GND), J2.B1A12 (GND), J3.GND1 (SH), J3.GND2 (SH), J4.2, J4.MP, J6.2, J6.9, J6.MP, MH1.1, MH2.1, MH3.1, MH4.1, PS1.1 (GNDin), PS2.1 (GNDin), R3.2, R8.2, R9.2, R11.2, R25.2, SW1.2, SW2.2, U1.1 (GND), U1.40 (GND), U1.41 (EP), U2.3 (AGND), U2.9 (AGND), U2.14 (AGND), U2.16 (AGND), U2.19 (AGND), U2.29 (GND), U2.48 (AGND), U4.2 (GND), U5.2 (GND1), U5.7 (GND1), U5.8 (GND1), U6.2 (GND1), U6.7 (GND1), U6.8 (GND1), U7.3 (-VDC), U8.2 (GND), U9.1 (GND), Y1.2, Y1.4
GNDISO: C19.2, C20.2, D1.2 (GND), J1.1 (SHIELD), J1.6 (SHELL6), J1.7 (SHELL7), J1.G (SHELL), J7.1, J7.MP, PS1.3 (GNDout), R21.2, U5.9 (GND2), U5.10 (GND2), U5.15 (GND2)
GNDISO2: C24.2, C25.2, D7.2 (GND), J5.1 (SHIELD), J5.6 (SHELL6), J5.7 (SHELL7), J5.G (SHELL), J8.1, J8.MP, PS2.3 (GNDout), R23.2, U6.9 (GND2), U6.10 (GND2), U6.15 (GND2)
IO0: R2.2, SW1.1, U1.27 (IO0)
LED_B: R16.1, U1.7 (IO7)
LED_G: R14.1, U1.38 (IO2)
LED_R: R13.1, U1.39 (IO1)
LED_W: R17.1, U1.8 (IO15)
LED_Y: R15.1, U1.6 (IO6)
MISO: U1.21 (IO13), U2.34 (MISO)
MOSI: U1.19 (IO11), U2.35 (MOSI)
unnamed: R3.1, U2.10 (EXRES1)
unnamed: J3.11 (LEDYA), R5.2
unnamed: R24.2, R25.1, U9.4 (PR1)
unnamed: D2.2 (A), R13.2
unnamed: D3.2 (A), R14.2
unnamed: D4.2 (A), R15.2
unnamed: D5.2 (A), R16.2
unnamed: D6.2 (A), R17.2
S3_RX: J6.8, U1.36 (RXD0)
S3_TX: J6.7, U1.37 (TXD0)
SCLK: U1.20 (IO12), U2.33 (SCLK)
TOCAP: C6.1, U2.20 (TOCAP)
USB_DM: J2.A7 (DN1), J2.B7 (DN2), U1.13 (IO19), U8.3 (IO2), U8.4 (IO2)
USB_DP: J2.A6 (DP1), J2.B6 (DP2), U1.14 (IO20), U8.1 (IO1), U8.6 (IO1)
VISO: C20.1, FB2.1, PS1.4 (VOUT)
VISO2: C25.1, FB3.1, PS2.4 (VOUT)
VISO2_DRV: C24.1, FB3.2, R22.2, U6.16 (VCC2)
VISO_DRV: C19.1, FB2.2, R20.2, U5.16 (VCC2)
VPOE+: D10.1 (K), J3.9 (POE_VP), U7.5 (VIN+), U7.6 (VIN+)
VPOE-: D10.2 (A), J3.10 (POE_VN), U7.7 (VIN-), U7.8 (VIN-)
W5500_1V2: C4.1, C5.1, U2.22 (1V2O)
XI: C12.1, U2.30 (XI), Y1.1
XO: C13.1, U2.31 (XO), Y1.3

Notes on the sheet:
U1 ESP32-S3-WROOM-1 + reset / boot
USB-C (J2) + ESD (U8) -> S3 native USB (USB-Serial-JTAG on IO19/IO20)
U4 SY8089 5V -> 3.3V buck
Isolated DMX universe 2 (U6 ISO3086 / PS2 / XLR J5)
Headers: display (J4) / expansion (J6) / DMX-out (J7,J8)
U2 W5500 Ethernet + 25MHz crystal + HY931147C magjack (J3)
PoE PD (U7) + 5V priority mux (U9 TPS2116, PoE preferred)
Isolated DMX universe 1 (U5 ISO3086 / PS1 / XLR J1)
Status LEDs (direct on S3 GPIOs)
Mounting holes (chassis GND)
Misc

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

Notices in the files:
README.md:
License:
MIT. Do whatever you want, attribution appreciated.
License: Apache-2.0
[ESP32Async/ESPAsyncWebServer](https://github.com/ESP32Async/ESPAsyncWebServer) | git | LGPL-3.0 | The whole HTTP side: web UI, REST API, WebSocket live channels, OTA upload, and the first-run setup portal. All non-blocking, so DMX keeps clocking while someone browses the config page.
[Adafruit NeoPixel](https://github.com/adafruit/Adafruit_NeoPixel) | `^1.12.3` | LGPL-3.0 | Drives the WS2812 RGB status LED (DevKit boards, and any DIY build with an addressable LED).
